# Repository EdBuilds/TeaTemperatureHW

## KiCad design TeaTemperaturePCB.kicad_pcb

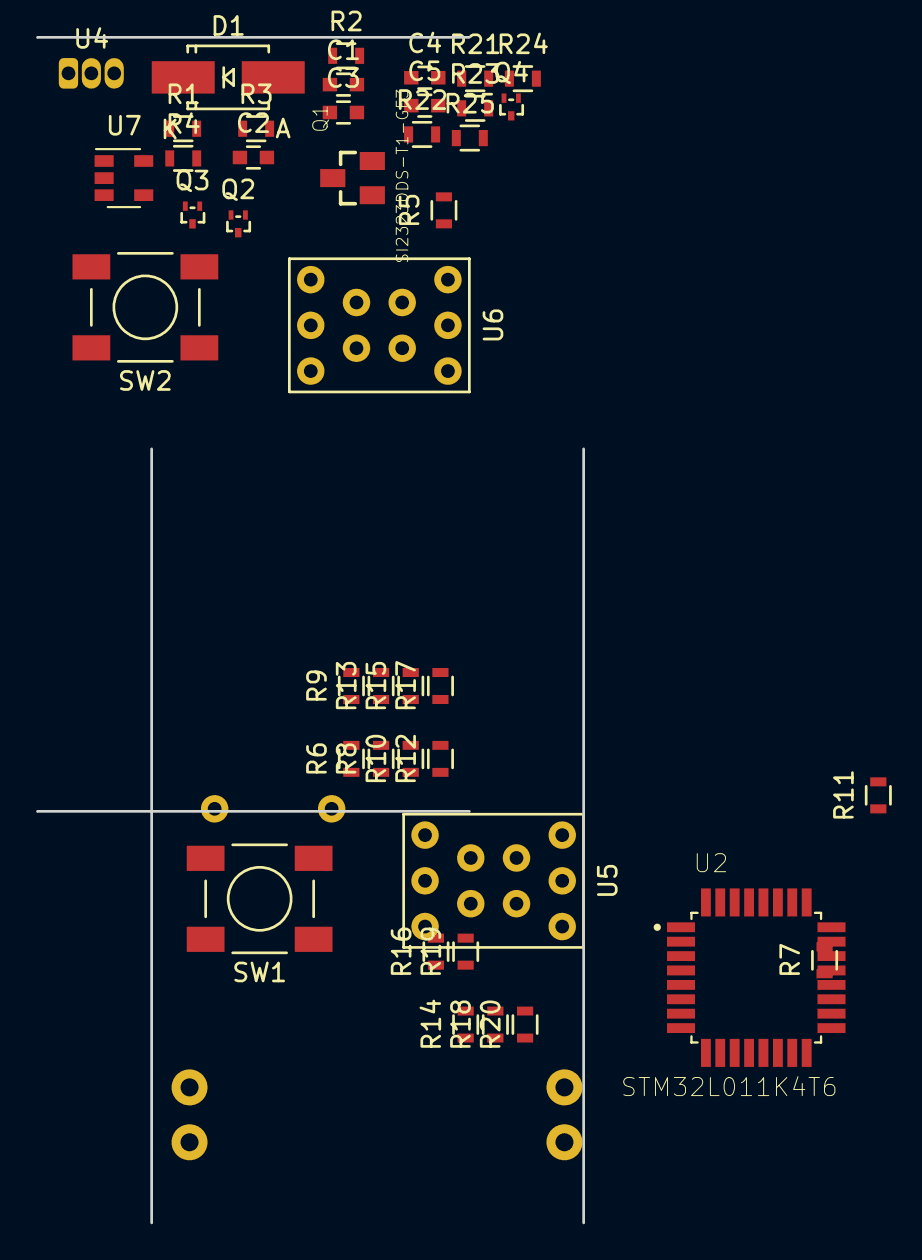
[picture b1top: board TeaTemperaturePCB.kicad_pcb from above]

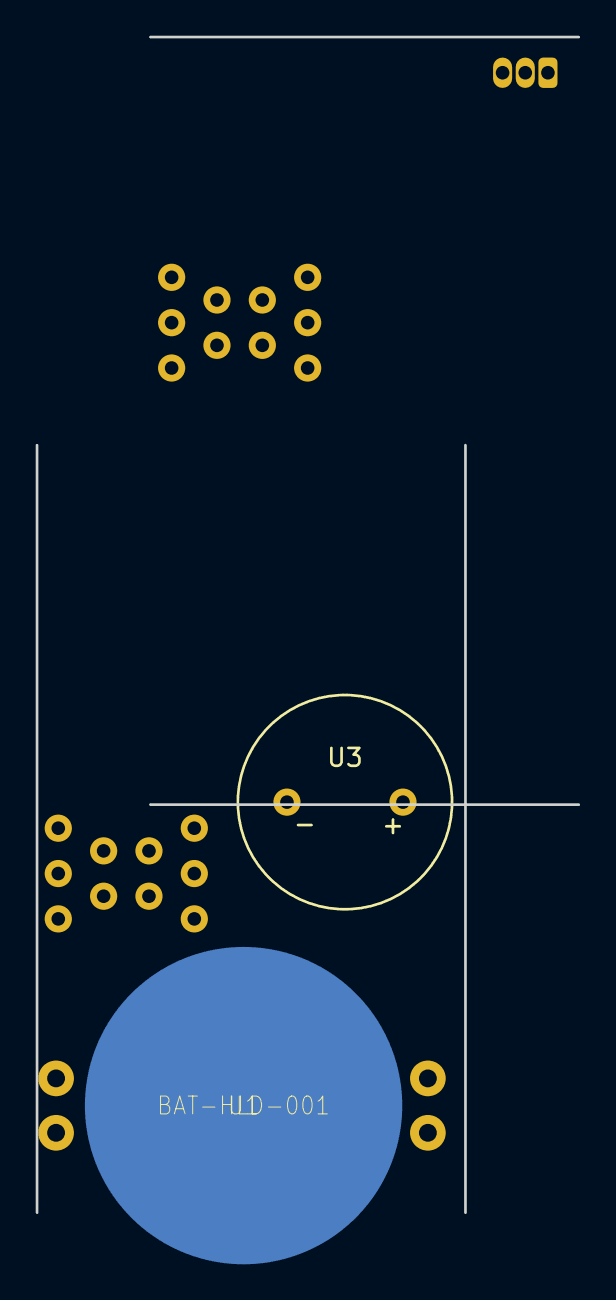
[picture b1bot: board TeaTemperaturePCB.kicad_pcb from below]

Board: 2 copper layers, 30.3 x 65.9 mm, 44 parts (2 on the bottom side), 42 nets, no tracks yet.

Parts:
C1, C2, C3, C4: 0.1uF; C_0603
C5: 10uF; C_0603
D1: S1G-K R2G; SMA_Handsoldering
Q1: SI2323DDS-T1-GE3; SOT23
Q2, Q3, Q4: SSM3K35AMFV; SOT-723
R1, R3, R22, R24, R25: 250K; R_0603
R2, R4, R21, R23: 10K; R_0603
R5, R6, R7, R8, R9, R10, R11, R12, R13, R14, R15, R16, R17, R18, R19, R20: 750; R_0603
SW1, SW2: LL3301FF065QJ
U1: BAT-HLD-001; BAT-HLD-001-THM
U2: STM32L011K4T6; QFP80P900X900X160-32N
U3: ABT-407-RC
U4: LMT84LPGM
U5, U6: TDSR0760
U7: AP7354D-18W5-7; SOT-23-5

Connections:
+1V8: C2.1, C3.1, U2.5, U4.3, U7.5
+BATT: Q1.2, U1.+@1, U1.+@2
/BATT_MEAS: R24.1, R25.2
/BATT_MEAS_CTRL: R22.2, R23.2
/BUZZER_CTRL: R1.2, R2.2
/DISP_BLK_1_EN: U5.3, U5.8
/DISP_BLK_2_EN: U6.3, U6.8
/DISP_SEG_A: R5.2, R13.2, U2.22
/DISP_SEG_B: R6.2, R14.2, U2.14
/DISP_SEG_C: R7.2, R15.2, U2.30
/DISP_SEG_D: R8.2, R16.2, U2.29
/DISP_SEG_DP: R12.2, R20.2, U2.28
/DISP_SEG_E: R9.2, R17.2, U2.15
/DISP_SEG_F: R10.2, R18.2, U2.18
/DISP_SEG_G: R11.2, R19.2, U2.21
/MCO: U2.2, U2.6
/THERM_CTRL: R3.2, R4.2
GND: C1.2, C2.2, C3.2, C4.2, C5.2, Q1.1, Q2.2, Q3.2, Q4.2, R1.1, R3.1, R21.1, R22.1, U1.-, U2.16, U2.32, U7.2
unnamed: D1.2, Q2.3, U3.2
unnamed: Q2.1, R2.1
unnamed: Q3.1, R4.1
unnamed: Q3.3, U4.1
unnamed: Q4.1, R23.1
unnamed: Q4.3, R25.1
unnamed: R5.1, U6.7
unnamed: R6.1, U6.6
unnamed: R7.1, U6.4
unnamed: R8.1, U6.2
unnamed: R9.1, U6.1
unnamed: R10.1, U6.10
unnamed: R11.1, U6.9
unnamed: R12.1, U6.5
unnamed: R13.1, U5.7
unnamed: R14.1, U5.6
unnamed: R15.1, U5.4
unnamed: R16.1, U5.2
unnamed: R17.1, U5.1
unnamed: R18.1, U5.10
unnamed: R19.1, U5.9
unnamed: R20.1, U5.5
unnamed: R21.2, U2.31
VCC: C1.1, C4.1, C5.1, D1.1, Q1.3, R24.2, SW1.1, SW2.1, U2.1, U2.17, U3.1, U7.1, U7.3

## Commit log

2018-10-26 Main components added
2018-11-17 Added kicad project
